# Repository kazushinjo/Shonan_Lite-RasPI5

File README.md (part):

# Shonan for RasPI5

Raspberry Pi 5 + ADALM-PlutoによるDVB-S2 DATV送受信タッチGUIシステム。
本体は`pi5/`配下(Python/PyQt5、eglfs直描画)。

A touch-screen GUI system for DVB-S2 DATV transmission and reception using a Raspberry Pi 5 and an ADALM-Pluto.
The application lives under `pi5/` (Python/PyQt5, rendered directly via eglfs).

> 本READMEは日本語と英語を併記しています。各節で日本語の後に英語が続きます。
> This README is written in both Japanese and English. In each section, the Japanese text is followed by the English text.

> [!IMPORTANT]
> **Plutoのユーザー名(`root`)・パスワード(`analog`)はデフォルト値のまま変更しないでください。**
> 本アプリとLangstone V3は、SSHでPlutoにログインしてリブートしています(アプリ起動時・アプリ再起動・
> 機器試験・Langstone終了時)。変更するとPlutoをリブートできなくなります。
>
> **Keep the Pluto's username (`root`) and password (`analog`) at their default values.**
> This app and Langstone V3 log in to the Pluto via SSH to reboot it (at app start, app restart,
> equipment test and Langstone exit). If they are changed, the Pluto cannot be rebooted.

## 主な機能 / Features

- **送信**: 周波数・シンボルレート(333〜2000 kS/s)・FEC・変調方式(QPSK/8PSK)・TX出力を画面で設定し、
  Pluto内蔵の`pluto_dvb`でDVB-S2送信する。FECは変調方式ごとに実際に動作する組み合わせだけを選べる
  (QPSK: 1/2・3/5・8/9、8PSK: 3/5・8/9)。送信映像はフルHD(1920x1080)固定。
- **映像ソース**: USBカメラ・画像ファイル(静止画を反復送信)・テストパターンから選ぶ。カメラ選択時は
  「撮影」ボタンで静止画(JPG、`~/Pictures/Shonan_Lite/`)を撮り、そのまま送信画像に使える。
  コールサイン・備考を文字サイズ・文字色を選んで映像へ焼き込める(日時も表示)。
- **受信**: GNU Radio(gr-dvbs2rx)によるPi 5上での復調。LOCK状態・ビットレート・パケット数/エラー数を表示。
- **RSSI測定**: 周波数を掃引して受信レベルをグラフ表示する。オンデバイス復調OFF(通常運用)では
  相手局の電波を測り、ON(テスト用)では自局もテストパターンで自動送信して自分の信号を測る。
- **プリセット**: 現在の設定を5件まで登録・呼び出し(プリセット1は未登録の間RFループバック試験用)。
- **10GHz受信(LNB)**: Home画面の衛星をタップすると、Langstone V3を10236.5 MHz表示・
  Pluto受信486.5 MHz(LNB局部発振9750 MHz)の受信専用バンドで開く(下記参照)。
  Shonan_Lite(DATV)でも、周波数画面で「10GHz帯」を押すとLNBを使用するか確認し、使用する場合は
  表示周波数10.2365 GHz・Pluto受信486.5 MHzで受信する(受信専用、送信不可。「いいえ」なら従来どおり10180 MHz)。
- **その他**: Pluto URIの自動検出、日本語/英語表示、日本語オンスクリーンキーボード、アプリ内Help、
  機器試験、起動時のアプリ選択(Shonan_Lite / Langstone V3)。

<!-- English -->

- **Transmit**: Set the frequency, symbol rate (333–2000 kS/s), FEC, modulation (QPSK/8PSK) and TX power on screen,
  and transmit DVB-S2 with `pluto_dvb` running inside the Pluto. Only FEC rates that actually work with each
  modulation can be selected (QPSK: 1/2, 3/5, 8/9; 8PSK: 3/5, 8/9). The transmitted video is fixed at Full HD (1920x1080).
- **Video source**: Choose from a USB camera, an image file (a still image transmitted repeatedly) or a test pattern.
  With the camera selected, the "Capture" button takes a still image (JPG, `~/Pictures/Shonan_Lite/`) that can be
  used directly as the transmit image. A callsign and a note can be burned into the video with a selectable
  text size and color (the date and time are shown as well).
- **Receive**: Demodulation on the Pi 5 with GNU Radio (gr-dvbs2rx). Shows LOCK status, bit rate and packet/error counts.
- **RSSI measurement**: Sweeps the frequency and graphs the received level. With on-device demodulation OFF
  (normal operation) it measures the other station's signal; with it ON (for testing) the station also transmits
  a test pattern automatically and measures its own signal.
- **Presets**: Save and recall up to 5 sets of settings (preset 1 is used for the RF loopback test while it is empty).
- **10 GHz reception (LNB)**: Tapping the satellite on the Home screen opens Langstone V3 on a receive-only band
  showing 10236.5 MHz, with the Pluto receiving at 486.5 MHz (LNB local oscillator 9750 MHz). See below.
  In Shonan_Lite (DATV) as well, pressing "10GHz Band" on the Frequency screen asks whether to use an LNB;
  if so, it receives with the displayed frequency 10.2365 GHz and the Pluto receiving at 486.5 MHz
  (receive only, no transmit; "No" keeps 10180 MHz as before).
- **Other**: Automatic Pluto URI detection, Japanese/English display, Japanese on-screen keyboard, in-app Help,
  equipment test, and application selection at boot (Shonan_Lite / Langstone V3).

## スクリーンショット / Screenshots

実機(7インチLCD、800x480)の画面。映像はすべてテストパターンで撮影している。

Screens from the actual device (7-inch LCD, 800x480). All video was captured using the test pattern.

| Home画面 / Home | 送信画面 / TX | 受信画面 / RX | RSSI測定 / RSSI |
| --- | --- | --- | --- |
|  |  |  |  |

| 映像ソース / Video source | 変調方式 / Modulation | 出力設定 / Stream output | プリセット / Presets |
| --- | --- | --- | --- |
|  |  |  |  |

各画面の操作方法は、アプリ内の「ヘルプ」または操作説明書
[`pi5/docs/shonan_pi5_operation_manual.docx`](pi5/docs/shonan_pi5_operation_manual.docx)を参照。

For how to operate each screen, see the in-app "Help" or the operation manual
[`pi5/docs/shonan_pi5_operation_manual.docx`](pi5/docs/shonan_pi5_operation_manual.docx) (in Japanese).

## インストール / Installation

### 事前に準備するもの / What you need

- Raspberry Pi 5本体
- microSDカードまたはNVMe SSD(Pi5の起動ストレージ)
- 書き込み用PC(Windows/Mac/Linuxいずれか)とmicroSDカードリーダー等
- ADALM-Pluto(DATVファームウェア導入済み)がPi5とEthernet同一ネットワークに
  接続されていること(★`install.sh`実行時点では未接続でもよい。あくまで
  ソフトウェア導入のみで、実運用時に必要)
- 送信映像用USBカメラ・オーディオ機器(任意、無くてもテストパターン映像で
  動作確認できる)

<!-- English -->

- A Raspberry Pi 5
- A microSD card or NVMe SSD (the Pi 5 boot storage)
- A PC for writing the image (Windows, Mac or Linux) and a microSD card reader, etc.
- An ADALM-Pluto (with DATV firmware installed) connected to the same Ethernet network as the Pi 5
  (★It does not need to be connected when running `install.sh`; that only installs software.
  It is required for actual operation.)
- A USB camera and audio devices for the transmitted video (optional; without them you can still
  check operation with the test pattern)

### 0. Raspberry Pi OSのインストール / Installing Raspberry Pi OS

Pi5本体に、あらかじめRaspberry Pi OSをインストールしておく。

1. PCで[Raspberry Pi Imager](https://www.raspberrypi.com/software/)を起動する。
2. 「デバイスを選択」で **Raspberry Pi 5** を選ぶ。
3. 「OSを選択」で **Raspberry Pi OS (64-bit)** を選ぶ
   (★32bit版は不可。下記「実行条件」参照)。
4. 「ストレージを選択」で書き込み先のmicroSD/NVMeを選ぶ。
5. 歯車アイコン(詳細設定)で、ホスト名・ユーザー名/パスワード・Wi-Fi・SSH有効化を
   事前設定しておくと、初回起動後すぐSSH接続できる。
6. 「書き込む」を実行し、完了後microSD/NVMeをPi5に取り付けて起動する。
7. PCから`ssh <ユーザー名>@<ホスト名>.local`で接続できることを確認する。

Install Raspberry Pi OS on the Pi 5 beforehand.

1. Launch [Raspberry Pi Imager](https://www.raspberrypi.com/software/) on your PC.
2. Under "Choose Device", select **Raspberry Pi 5**.
3. Under "Choose OS", select **Raspberry Pi OS (64-bit)**
   (★The 32-bit version is not supported. See "Requirements" below).
4. Under "Choose Storage", select the target microSD/NVMe.
5. If you preset the hostname, username/password, Wi-Fi and SSH in the gear icon (advanced options),
   you can connect via SSH right after the first boot.
6. Click "Write". When done, attach the microSD/NVMe to the Pi 5 and boot it.
7. Confirm that you can connect from your PC with `ssh <username>@<hostname>.local`.

### 0.5 Plutoのネットワーク設定(USB_ETHERNET) / Pluto network settings (USB_ETHERNET)

ADALM-Pluto(DATVファームウェア導入済み)をPi5と同じEthernetネットワークに
接続するには、あらかじめPluto側のUSB_ETHERNETインターフェースに固定IPを
設定しておく。

1. PlutoをPCとUSBケーブルで接続する(USB Mass Storageとして認識される)。
2. Plutoのドライブ直下にある`config.txt`をテキストエディタで開く。
3. `[USB_ETHERNET]`セクションの`ipaddr_eth`と`netmask_eth`を、Pi5と同じ
   サブネット内の値に設定する(例、Pi5が`192.168.0.80/24`の場合)。
4. `config.txt`を保存し、PlutoのドライブをPCから安全に取り出す(eject)。
   Plutoが自動的に再起動し、新しいIPアドレスで起動する。
5. Pi5の設定画面「送信先 (Pluto Tx)」に、ここで設定した`ipaddr_eth`の値
   (下記例では`192.168.0.51`)を入力する。

To connect the ADALM-Pluto (with DATV firmware) to the same Ethernet network as the Pi 5,
assign a static IP to the Pluto's USB_ETHERNET interface beforehand.

1. Connect the Pluto to your PC with a USB cable (it appears as a USB Mass Storage device).
2. Open `config.txt` in the root of the Pluto drive with a text editor.
3. Set `ipaddr_eth` and `netmask_eth` in the `[USB_ETHERNET]` section to values in the same subnet
   as the Pi 5 (example below for a Pi 5 at `192.168.0.80/24`).
4. Save `config.txt` and safely eject the Pluto drive from the PC.
   The Pluto reboots automatically and comes up with the new IP address.
5. Enter the `ipaddr_eth` value set here (`192.168.0.51` in the example below) into
   "Destination (Pluto Tx)" on the Pi 5 settings screen.

```ini
[USB_ETHERNET]
ipaddr_eth = 192.168.0.51
netmask_eth = 255.255.255.0
```

★Plutoのユーザー名(`root`)とパスワード(`analog`)は変更しないこと(理由は冒頭の「IMPORTANT」を参照)。

★Do not change the Pluto's username (`root`) and password (`analog`) (see "IMPORTANT" at the top for why).

★USB直結時のUSB CDCネットワーク(`[NETWORK]`セクション、既定`192.168.2.1`)
とは別の設定である。`[USB_ETHERNET]`は、Pluto(Pluto+)のUSB OTGポートに
挿したUSB-Ethernetアダプタに割り当てるIPアドレスで、これによりPlutoが
Pi5と同じLAN(Ethernet)上のノードとして直接通信できるようになる。
設定ファイルの詳細は
[ADI公式Wiki](https://wiki.analog.com/university/tools/pluto/users/customizing)
を参照。

★This is separate from the USB CDC network used for a direct USB connection (the `[NETWORK]` section,
default `192.168.2.1`). `[USB_ETHERNET]` is the IP address assigned to a USB-Ethernet adapter plugged
into the Pluto (Pluto+) USB OTG port, which lets the Pluto communicate directly as a node on the same
LAN (Ethernet) as the Pi 5. For details of the configuration file, see the
[official ADI Wiki](https://wiki.analog.com/university/tools/pluto/users/customizing).

### 1. install.shの実行 / Running install.sh

本リポジトリはpublicのため、HTTPS clone(`install.sh`既定)でそのまま取得できる。
まずPi5へSSHでログインする(`<...>`の部分はご自身の環境の値に置き換える):

This repository is public, so it can be fetched as-is with an HTTPS clone (the `install.sh` default).
First log in to the Pi 5 via SSH (replace the `<...>` parts with values for your environment):

```sh
ssh <Pi5のユーザー名 / Pi 5 username>@<Pi5のIPアドレスまたはホスト名 / Pi 5 IP address or hostname>
# 例 / Example: ssh pi@192.168.0.80
```

ログイン後、Pi5上で:

After logging in, on the Pi 5:

```sh
# gitが未導入の場合は先に用意する(初回のみ)
# Install git first if it is not installed yet (first time only)
sudo apt-get update && sudo apt-get install -y git

git clone https://github.com/kazushinjo/Shonan_Lite-RasPI5.git
cd Shonan_Lite-RasPI5
./pi5/scripts/install.sh
```

`install.sh`自身も0/9でgit未導入の場合は自動導入する。以降のアップデート時も
このコマンドを再実行するだけでよい(`REPO_BRANCH`環境変数で取得するブランチを
指定できる。既定は`main`)。

`install.sh` itself also installs git automatically at step 0/9 if it is missing. For later updates,
simply re-run this command (the branch to fetch can be specified with the `REPO_BRANCH` environment
variable; the default is `main`).

★自分のフォークやプライベートなミラーからSSH経由で取得したい場合は、
`REPO_URL=git@github.com:<user>/<repo>.git ./pi5/scripts/install_ssh.sh`を使う
(SSH鍵が未登録ならその場で生成し、GitHubへの登録案内を表示して終了する)。

★To fetch from your own fork or a private mirror over SSH, use
`REPO_URL=git@github.com:<user>/<repo>.git ./pi5/scripts/install_ssh.sh`
(if no SSH key is registered, it generates one on the spot, shows instructions for registering it
with GitHub, and exits).

Pi5がGitHubへ到達できない環境(オフライン現場等)では、scp/USB等で転送済みの
ローカルクローンから展開する`install_local.sh`を使う(GitHubへのアクセスは
一切発生しない)。ソース取得部分がgit clone/pullではなくrsyncでのローカル
コピーに変わる以外は`install.sh`と同じ:

Where the Pi 5 cannot reach GitHub (e.g. offline sites), use `install_local.sh`, which installs from
a local clone already transferred via scp/USB etc. (no access to GitHub occurs at all). It is the same
as `install.sh` except that the source is obtained by a local rsync copy instead of git clone/pull:

```sh
./pi5/scripts/install_local.sh
```

さらに、PC側(Windows Git Bash/Mac/Linux)にあらかじめ作っておいたローカル
クローンから、Pi5への転送とインストールを1コマンドで行う`deploy_to_pi5.sh`
もある。PC側でこのリポジトリをclone済みの状態で:

There is also `deploy_to_pi5.sh`, which transfers and installs to the Pi 5 in a single command from a
local clone prepared on your PC (Windows Git Bash/Mac/Linux). With this repository cloned on the PC:

```sh
./pi5/scripts/deploy_to_pi5.sh
# Pi5のIPアドレス/ホスト名: 192.168.1.50   ← 入力 / enter
# Pi5のユーザー名 [pi]:                    ← 入力(空Enterでpi) / enter (empty Enter = pi)
```

を実行すると、Pi5のIPアドレス・ユーザー名の入力だけで、
1. ローカルクローンの中身(`.git`除く)をtar+ssh経由でPi5の`~/shonan-pi5-src`へ転送
2. Pi5上で`install_local.sh`を実行

まで自動で進む。追加ツール(sshpass/rsync)は使わず標準のssh/scp/tarのみで
動くため、Pi5への接続が発生する上記1・2のタイミングでそれぞれ標準のsshパス
ワードプロンプトが表示され、都度パスワードの入力が必要(合計2回。ビルドが
長時間に及ぶ場合、`sudo`のキャッシュが切れて追加でパスワードを求められる
こともある)。都度の入力自体を無くしたい場合はPi5にSSH公開鍵を登録し、
パスワード認証を使わない構成にする。

Just by entering the Pi 5 IP address and username, it automatically:
1. Transfers the contents of the local clone (excluding `.git`) to `~/shonan-pi5-src` on the Pi 5 via tar+ssh
2. Runs `install_local.sh` on the Pi 5

It uses only standard ssh/scp/tar with no extra tools (sshpass/rsync), so the standard ssh password
prompt appears at each of steps 1 and 2 above, where a connection to the Pi 5 is made, and you need
to enter the password each time (twice in total; if the build takes a long time, the `sudo` cache may
expire and ask for the password again). To avoid entering it every time, register an SSH public key
on the Pi 5 and do not use password authentication.

`SHONAN_INSTALL_DIR`・`SKIP_JA_KEYBOARD`・`SKIP_GNURADIO_BUILD`・
`SKIP_LANGSTONE_BUILD`をPC側で環境変数指定すると、Pi5側の`install_local.sh`
実行にもそのまま反映される:

Environment variables `SHONAN_INSTALL_DIR`, `SKIP_JA_KEYBOARD`, `SKIP_GNURADIO_BUILD` and
`SKIP_LANGSTONE_BUILD` set on the PC side are passed through to `install_local.sh` on the Pi 5:

```sh
SKIP_JA_KEYBOARD=1 SKIP_GNURADIO_BUILD=1 ./pi5/scripts/deploy_to_pi5.sh
```

日本語入力ビルド・受信(RX)用GNU Radio/gr-dvbs2rxビルド・Langstone V3ビルドは
それぞれ省略して時間短縮できる(省略した機能は使えなくなる):

The Japanese input build, the GNU Radio/gr-dvbs2rx build for reception (RX) and the Langstone V3
build can each be skipped to save time (skipped features will not be available):

```sh
SKIP_JA_KEYBOARD=1 SKIP_GNURADIO_BUILD=1 SKIP_LANGSTONE_BUILD=1 ./pi5/scripts/install.sh
```

環境変数で挙動を変更できる。

The behavior can be changed with environment variables.

| 変数 / Variable | 既定値 / Default | 効果 / Effect |
| --- | --- | --- |
| `SHONAN_INSTALL_DIR` | `$HOME/shonan-pi5` | リポジトリのclone/pull(またはコピー)先ディレクトリ<br>Directory the repository is cloned/pulled (or copied) into |
| `LOCAL_SOURCE_DIR` | (未設定 / unset) | 設定時、ソース取得をGitHubのclone/pullではなく指定ディレクトリからのrsyncコピーに切り替える(`install_local.sh`が自動設定)<br>When set, obtains the source by rsync copy from the given directory instead of clone/pull from GitHub (set automatically by `install_local.sh`) |
| `QTVK_BUILD_DIR` | `/tmp/qtvirtualkeyboard-src` | Qt Virtual Keyboardのビルド作業ディレクトリ<br>Build working directory for Qt Virtual Keyboard |
| `GR_DVBS2RX_BUILD_DIR` | `$HOME/gr-dvbs2rx` | gr-dvbs2rxのビルド作業ディレクトリ<br>Build working directory for gr-dvbs2rx |
| `SKIP_JA_KEYBOARD` | `0` | `1`で日本語入力ビルド(3/9)を省略<br>`1` skips the Japanese input build (3/9) |
| `SKIP_GNURADIO_BUILD` | `0` | `1`で受信(RX)用GNU Radio/gr-dvbs2rxビルド(4/9)を省略(受信機能は動作しなくなる)<br>`1` skips the GNU Radio/gr-dvbs2rx build for reception (4/9) (reception will not work) |
| `SKIP_LANGSTONE_BUILD` | `0` | `1`でLangstone V3のビルド(5/9)を省略<br>`1` skips the Langstone V3 build (5/9) |

`install.sh`は以下の9ステップを順に実行する(`set -euo pipefail`のため、
いずれかが失敗した時点で即座に停止する)。

`install.sh` runs the following 9 steps in order (because of `set -euo pipefail`, it stops
immediately as soon as any step fails).

| ステップ / Step | 内容 / Description |
| --- | --- |
| 0/9 | 前提条件の確認(git/SSH鍵の有無を確認し、無ければ案内して終了)<br>Check prerequisites (checks for git/SSH key; if missing, shows guidance and exits) |
| 1/9 | ソース取得(`git clone`または`git pull`)<br>Fetch the source (`git clone` or `git pull`) |
| 2/9 | 実行時依存パッケージのインストール(apt)<br>Install runtime dependency packages (apt) |
| 3/9 | 日本語入力(OpenWnn)対応版Qt Virtual Keyboardのビルド(既定で実施、実測10〜20分程度)<br>Build Qt Virtual Keyboard with Japanese input (OpenWnn) support (done by default, about 10–20 minutes measured) |
| 4/9 | 受信(RX)用GNU Radio + gr-dvbs2rxの導入<br>Install GNU Radio + gr-dvbs2rx for reception (RX) |
| 5/9 | Langstone V3(SDRトランシーバー)のビルド<br>Build Langstone V3 (SDR transceiver) |
| 6/9 | 起動時コンソール表示の抑制<br>Suppress the console display at boot |
| 7/9 | reboot/shutdown/起動アプリ切替のパスワード無し実行を許可(sudoers.d)<br>Allow reboot/shutdown/boot-app switching without a password (sudoers.d) |
| 8/9 | 電源電圧警告(稲妻アイコン)表示の抑制(`/boot/firmware/config.txt`)<br>Suppress the under-voltage warning (lightning icon) (`/boot/firmware/config.txt`) |
| 9/9 | systemdサービス登録(`shonan-gui.service`/`langstone.service`/`shonan-boot-menu.service`)<br>Register systemd services (`shonan-gui.service`/`langstone.service`/`shonan-boot-menu.service`) |

途中で通信・電源が切れない環境で実行すること。完了後、起動のたびに
「Shonan_Lite / Langstone V3」を選ぶ全画面メニュー
(`shonan-boot-menu.service`)が自動起動する。選んだ側の`shonan-gui.service`/
`langstone.service`をsystemdに登録・起動する。あわせて
`/boot/firmware/config.txt`へ`avoid_warnings=1`(電源電圧警告アイコンの表示抑制)
を未設定なら自動で追記する(反映には再起動が必要)。

Run it in an environment where the network and power will not be interrupted. After completion,
a full-screen menu for choosing "Shonan_Lite / Langstone V3" (`shonan-boot-menu.service`) starts
automatically at every boot, and the selected `shonan-gui.service`/`langstone.service` is registered
with systemd and started. It also appends `avoid_warnings=1` (suppresses the under-voltage warning
icon) to `/boot/firmware/config.txt` if not already set (a reboot is required for it to take effect).

### インストール後の確認 / After installation

インストールが終わったら、まず実機のホーム画面から「ヘルプ」を開いて
使い方を確認する。画面構成、送受信の基本操作、設定項目、トラブルシュー
ティング等の各章が実機の現在の仕様に合わせてまとまっている。

After installation, first open "Help" from the Home screen on the device and review how to use it.
Chapters on the screen layout, basic TX/RX operation, settings, troubleshooting and more are kept up
to date with the current behavior of the device.

## 実機LCDの画面キャプチャー / Capturing the device LCD screen

### アプリ内蔵のスクリーンショット機能(推奨) / Built-in screenshot function (recommended)

Shonan_Lite(GUI)は起動中、Unixドメインソケット`/tmp/shonan-pi5-gui.sock`でコマンドを受け付ける。
`screenshot`を送ると、表示中の画面を`/tmp/shonan_lcd_actual.png`に保存する(GUIは止まらない)。
`navigate:<画面名>`で任意の画面へ移動できる(画面名: `home` `tx` `rx` `frequency` `rssi`
`symbolrate` `fec` `modulation` `videosource` `streamoutput` `rxgain` `txpower` `manual`
`settings` `testequipment` `presets`)。
`volume:<増減>`(例: `volume:+2`)は、ロータリーエンコーダを回したときと同じ音量変更を行う(音量ポップアップの確認用)。

While running, Shonan_Lite (GUI) accepts commands on the Unix domain socket `/tmp/shonan-pi5-gui.sock`.
Sending `screenshot` saves the current screen to `/tmp/shonan_lcd_actual.png` (the GUI does not stop).
`navigate:<screen>` moves to any screen (screens: `home` `tx` `rx` `frequency` `rssi`
`symbolrate` `fec` `modulation` `videosource` `streamoutput` `rxgain` `txpower` `manual`
`settings` `testequipment` `presets`).
`volume:<delta>` (e.g. `volume:+2`) changes the volume the same way as turning the rotary encoder (for checking the volume popup).

```bash
python3 -c "import socket,sys; s=socket.socket(socket.AF_UNIX); s.connect('/tmp/shonan-pi5-gui.sock'); s.sendall(sys.argv[1].encode()); s.close()" navigate:rssi
python3 -c "import socket,sys; s=socket.socket(socket.AF_UNIX); s.connect('/tmp/shonan-pi5-gui.sock'); s.sendall(sys.argv[1].encode()); s.close()" screenshot
```

起動直後は「アプリ起動時にPlutoも再起動しています…」の表示(最大25秒)が写ることがあるので、
起動から30秒ほど待ってから撮る。

Right after startup, the message "Rebooting the Pluto as the app starts…" (up to 25 seconds) may be
captured, so wait about 30 seconds after startup before taking a screenshot.

### kmsgrabによる取得 / Capturing with kmsgrab

Shonan_LiteはLCDへQt/DRMで直接描画しているため、`/dev/fb0`を読み出す方法では
起動コンソールなど、最終合成前の内容になることがある(素の色1色などになる)。
実際にLCDへ表示されている画面を取得する場合は、KMSのCRTC/Planeを指定して
`ffmpeg`の`kmsgrab`を使う。

Because Shonan_Lite draws directly to the LCD via Qt/DRM, reading `/dev/fb0` may give content from
before final composition, such as the boot console (e.g. a single plain color). To capture what is
actually displayed on the LCD, use `ffmpeg`'s `kmsgrab` specifying the KMS CRTC/Plane.

★`/dev/dri/card0`はモードセッティング非対応のスタブデバイスで、これを指定すると
`kmsgrab`が`Failed to set universal planes capability`/`Operation not supported`
で失敗する(実機で確認)。DSIパネルを実際に駆動しているのは**`/dev/dri/card1`**
なので、必ずこちらを指定する。

★`/dev/dri/card0` is a stub device without mode-setting support; specifying it makes `kmsgrab` fail
with `Failed to set universal planes capability`/`Operation not supported` (confirmed on the device).
The DSI panel is actually driven by **`/dev/dri/card1`**, so always specify that one.

まず実機で現在のCRTC/Plane IDを確認する(再起動などでIDが変わる場合がある):

First check the current CRTC/Plane IDs on the device (the IDs may change after a reboot, etc.):

```bash
kmsprint
```

現在の実機ではCRTC IDが`36`、Plane IDが`34`なので、以下でLCD画面をPNG化できる。
`sudo`のパスワード入力が必要になる。

On the current device the CRTC ID is `36` and the Plane ID is `34`, so the following saves the LCD
screen as a PNG. You will need to enter the `sudo` password.

```bash
sudo ffmpeg -y -hide_banner \
  -f kmsgrab -device /dev/dri/card1 \
  -crtc_id 36 -plane_id 34 -framerate 1 -i - \
  -vf hwdownload,format=bgr0 -frames:v 1 -update 1 /tmp/shonan_lcd_actual.png
```

MacなどのPCへコピーする:

Copy it to a PC such as a Mac:

```bash
scp pi@<Pi5のIPアドレス / Pi 5 IP address>:/tmp/shonan_lcd_actual.png \
  ~/Desktop/shonan_lcd_actual.png
```

`/dev/fb0`の直接取得は、LCDの最終表示を取得できない場合があるため、実機LCDの
スクリーンショットには使用しない。

Reading `/dev/fb0` directly may not capture the final LCD image, so do not use it for screenshots
of the device LCD.

### 実行条件 / Requirements

一般ユーザーが実行して`install.sh`が正常完了するには、以下が必要。

- **Raspberry Pi OS 64bit(aarch64)であること**(32bit版不可)
- **`git`が事前にインストール済み**であること
- **GitHub/apt配布ミラーへのインターネット到達性**
- **sudoが使える対話的な実行**(パスワード入力に応答できるtty)
- **`patch`コマンドが使えること**

詳細な各手順の解説・トラブルシュートは
[`pi5/docs/install_script_guide.md`](pi5/docs/install_script_guide.md)
(DOCX版: `pi5/docs/install_script_guide.docx`)を参照。

For `install.sh` to complete successfully when run by a regular user, the following are required:

- **Raspberry Pi OS 64-bit (aarch64)** (the 32-bit version is not supported)
- **`git` installed beforehand**
- **Internet access to GitHub and the apt mirrors**
- **Interactive execution with sudo available** (a tty that can answer password prompts)
- **The `patch` command available**

For a detailed explanation of each step and troubleshooting, see
[`pi5/docs/install_script_guide.md`](pi5/docs/install_script_guide.md)
(DOCX version: `pi5/docs/install_script_guide.docx`, in Japanese).

## Langstone V3(SDRトランシーバー)への切替 / Switching to Langstone V3 (SDR transceiver)

Pi5起動後にまず表示される「起動するアプリを選択してください」メニュー
(`shonan-boot-menu.service`)、またはShonan_Lite Home画面の「Langstone V3」
ボタンから、[g4eml/Langstone-V3](https://github.com/g4eml/Langstone-V3)
(VHF/UHF/マイクロ波帯SDRトランシーバー、ADALM-Pluto対応)へ切り替えられる。
Langstone V3はQt eglfsとは別に`/dev/fb0`を直接描画する独立アプリのため、
DATV送受信アプリとは同時起動できないが、**`shonan-gui.service`/
`langstone.service`/`shonan-boot-menu.service`がsystemdの`Conflicts=`で
互いに排他制御されているため、Pi5自体のrebootは不要**で
`systemctl start`だけで即座に切り替わる(以前はPi5ごとrebootしていたが、
`shonan-boot-menu.service`導入により不要になった)。

- Shonan_Lite Home画面の「Langstone V3」ボタン → Langstone V3が起動
  (現在稼働中のShonan_Liteプロセスはsystemdが自動停止)
- Langstone V3の設定メニュー内「BACK TO SHONAN_LITE」ボタン →
  Shonan_Lite Home画面に戻る

From the "Select the app to start" menu shown first after the Pi 5 boots (`shonan-boot-menu.service`),
or from the "Langstone V3" button on the Shonan_Lite Home screen, you can switch to
[g4eml/Langstone-V3](https://github.com/g4eml/Langstone-V3) (a VHF/UHF/microwave SDR transceiver
supporting the ADALM-Pluto). Langstone V3 is a standalone app that draws directly to `/dev/fb0`,
separately from Qt eglfs, so it cannot run at the same time as the DATV app. However,
**`shonan-gui.service`/`langstone.service`/`shonan-boot-menu.service` are mutually exclusive via
systemd `Conflicts=`, so no reboot of the Pi 5 is needed**; a `systemctl start` switches immediately
(previously the whole Pi 5 was rebooted, but this became unnecessary with `shonan-boot-menu.service`).

- "Langstone V3" button on the Shonan_Lite Home screen → Langstone V3 starts
  (systemd automatically stops the running Shonan_Lite process)
- "BACK TO SHONAN_LITE" button in the Langstone V3 settings menu →
  returns to the Shonan_Lite Home screen

切替時にPluto(とPA_Power/PTTコントローラの12V電源)は**再起動しない**
(以前は切替のたびにPlutoを再起動しており、数十秒かかっていた)。実機試験で、
DATV→Langstone→DATVとPlutoを再起動せずに切り替えても、Langstoneの送受信と
DATVの送受信(オンデバイス復調による自局信号のロック)が正常に動くことを確認した。
ただしLangstoneは受信中にPlutoの送信LO(`altvoltage1`)をpowerdownしたまま終了し、
そのままではDATV送信の電波が出ないため、「GOTO SHONAN_LITE」で戻るときは
Langstone側とShonan_Lite側の両方で送信LOを元に戻す。
Langstoneからの切替であることは`/tmp/shonan_switch_from_langstone`で伝え、
Shonan_Liteはこれがあるときだけ起動時のPluto再起動を省く(使ったら消すので、
その後のアプリ再起動やPi5の電源投入時は従来どおり再起動する)。Langstone側の
`run_pluto`は`/tmp/langstone_goto_shonan`があるとき、終了後のPluto再起動を省く。Plutoが`fmcomms2_source: Unable to refill buffer`のように
詰まった場合は、Home画面の「アプリ再起動」(Plutoも再起動する)で復旧できる。

The Pluto (and the 12 V supply of the PA_Power/PTT controller) is **not rebooted** when switching
(previously the Pluto was rebooted on every switch, which took tens of seconds). Device testing
confirmed that after switching DATV → Langstone → DATV without rebooting the Pluto, both Langstone
TX/RX and DATV TX/RX (locking onto the station's own signal with on-device demodulation) work
correctly. However, Langstone exits with the Pluto's TX LO (`altvoltage1`) still powered down while
receiving, which would leave DATV transmission with no RF output, so when returning via
"GOTO SHONAN_LITE" both the Langstone side and the Shonan_Lite side restore the TX LO.
A switch from Langstone is signaled by `/tmp/shonan_switch_from_langstone`, and Shonan_Lite skips the
Pluto reboot at startup only when it exists (it is deleted after use, so later app restarts and Pi 5
power-ups reboot the Pluto as before). On the Langstone side, `run_pluto` skips the Pluto reboot after
exiting when `/tmp/langstone_goto_shonan` exists. If the Pluto gets stuck, e.g. with
`fmcomms2_source: Unable to refill buffer`, it can be recovered with "Restart App" on the Home screen
(which also reboots the Pluto).

内部的には`~/.pi5_boot_mode_langstone`マーカーファイルの有無をsystemdの
`ConditionPathExists`で判定し、`shonan-gui.service`/`langstone.service`の
どちらを起動すべきかを決める(ブート時だけでなく、アプリ内からの切替時にも
マーカーを書き換えてから対象サービスを直接startする)。

Internally, systemd's `ConditionPathExists` checks for the `~/.pi5_boot_mode_langstone` marker file
to decide whether `shonan-gui.service` or `langstone.service` should start (not only at boot; when
switching from within an app, the marker is rewritten and the target service is started directly).

ウォーターフォール/スペクトラム表示は幅約512px→約790pxへ拡張済み
(FFT点数自体はGNU Radio側のfft_size=512のまま、SCALEPX()マクロで描画のみ
引き伸ばしている。帯域インジケータ・目盛り・タッチ判定も含め一貫して変換)。
横方向にはSQLボタン(x=30〜130)/Volボタン(x=660〜)と同じY帯で重なり広げる
余地が無かったため、スペクトラム欄の高さ(80→55px)とウォーターフォールの
表示履歴行数(130→90行)を縮めて表示位置を上に詰め、SQL/Vol/RITいずれとも
Y方向に重ならない帯(Y=130〜295)に収めることで横方向をほぼ画面全幅まで
広げた(実機で確認、詳細は下記パッチ参照)。
詳細は
[`pi5/docs/patches/langstone_v3_shonan_lite.patch`](pi5/docs/patches/langstone_v3_shonan_lite.patch)
(upstream差分)を参照。

The waterfall/spectrum display has been widened from about 512 px to about 790 px
(the number of FFT points stays at fft_size=512 on the GNU Radio side; only the drawing is stretched
by the SCALEPX() macro, applied consistently to the bandwidth indicator, scale and touch detection).
Since there was no room to widen it horizontally in the same Y band as the SQL button (x=30–130) and
Vol button (x=660–), the spectrum area height (80 → 55 px) and the number of waterfall history rows
(130 → 90) were reduced and the display moved up, fitting it into a band (Y=130–295) that does not
overlap SQL/Vol/RIT vertically, which allows it to extend to nearly the full screen width (confirmed
on the device). For details, see
[`pi5/docs/patches/langstone_v3_shonan_lite.patch`](pi5/docs/patches/langstone_v3_shonan_lite.patch)
(diff against upstream).

起動直後の受信設定の取りこぼしも修正済み。本家のGUIは、GNU Radioフローグラフが
受信設定用のFIFO(`/tmp/langstoneTRx`)を開く前にモード・フィルタ・オフセット等を送り、
届かなかった分を捨てていた。そのためフローグラフが初期値(USB・オフセット0等)のまま動き、
Sメーター・ノイズレベルが本来より高く出ることがあった(Shonan_Liteから切り替えた直後に
S2前後、MODEやBANDを操作し直すとS0になる、を実機で確認)。オフセット0ではLO直上に出る
PlutoのDC成分(DCのこぶ)を受信帯域内で拾うためで、正しい値はS0の方
(本来はLOを+50 kHzずらしてDC成分を避ける。TX→40 dBアッテネータ→RXの無信号状態でS0)。
起動時にフローグラフがFIFOを開くまで(最大20秒)待ってから設定を送るようにした
(`waitForFlowgraph()`)。なおSメーターの0点(`S-Meter Zero`)は既定値-80のままで、
絶対レベル(S9=-73 dBm等)としては未校正。

The loss of receive settings right after startup has also been fixed. The upstream GUI sent the mode,
filters, offset, etc. before the GNU Radio flowgraph opened its settings FIFO (`/tmp/langstoneTRx`)
and discarded whatever could not be delivered, so the flowgraph kept running with its defaults
(USB, offset 0, etc.) and the S-meter and noise level could read higher than they should (confirmed
on the device: about S2 right after switching from Shonan_Lite, S0 after pressing MODE or BAND again).
With offset 0 the receiver picks up the Pluto's DC component (the DC hump right at the LO) inside the
passband, so S0 is the correct reading (normally the LO is shifted by +50 kHz to avoid the DC
component; with TX → 40 dB attenuator → RX and no signal it reads S0).
At startup it now waits until the flowgraph opens the FIFO (up to 20 s) before sending the settings
(`waitForFlowgraph()`). Note that the S-meter zero (`S-Meter Zero`) is still at its default of -80,
so it is not calibrated as an absolute level (e.g. S9 = -73 dBm).

`g4eml/Langstone-V3`本家が更新された場合、`pi5/third_party/Langstone-V3/`を
直接上書きすると上記の改造が失われる。
[`pi5/scripts/update_langstone_from_upstream.sh`](pi5/scripts/update_langstone_from_upstream.sh)
を実行すると、本家を読み取り専用でclone → このパッチを適用 →
成功した場合のみ`pi5/third_party/Langstone-V3/`を置き換える(本家への
書き込みは一切行わない)。パッチが当たらない場合は改造箇所と本家の変更が
衝突しているため、エラーで止まり手動マージが必要になる。

When upstream `g4eml/Langstone-V3` is updated, overwriting `pi5/third_party/Langstone-V3/` directly
would lose the modifications above. Running
[`pi5/scripts/update_langstone_from_upstream.sh`](pi5/scripts/update_langstone_from_upstream.sh)
clones upstream read-only → applies this patch → replaces `pi5/third_party/Langstone-V3/` only if
that succeeds (nothing is ever written to upstream). If the patch does not apply, the modifications
conflict with upstream changes; it stops with an error and a manual merge is required.

### 10GHz受信(LNB) — Home画面の衛星をタップ / 10 GHz reception (LNB) — tap the satellite on the Home screen

Home画面の背景右側の衛星をタップすると、Langstone V3を**10GHz受信用のバンド**で
開く(普通の「Langstone」カードと同じく、Plutoは再起動しない)。アンテナ側で
**LNB(局部発振 9750 MHz)**により周波数を下げて受信する前提の設定で、
LangstoneのトランスバーターのオフセットとしてLNBの局部発振周波数を設定している。

Tapping the satellite on the right side of the Home screen background opens Langstone V3 on a
**band for 10 GHz reception** (as with the normal "Langstone" card, the Pluto is not rebooted).
The settings assume the frequency is down-converted at the antenna by an **LNB (local oscillator
9750 MHz)**, and the LNB local oscillator frequency is set as Langstone's transverter offset.

| 項目 / Item | 値 / Value |
| --- | --- |
| 画面の表示周波数<br>Displayed frequency | 10236.500 MHz(10.2365 GHz、画面に「XVTR」と表示)<br>10236.500 MHz (10.2365 GHz, "XVTR" shown on screen) |
| Plutoの受信周波数<br>Pluto receive frequency | 486.5 MHz(= 10236.5 − 9750) |
| 受信オフセット<br>Receive offset | −9750 MHz(LNB 局部発振 9750 MHz)<br>−9750 MHz (LNB local oscillator 9750 MHz) |
| 受信モード<br>Receive mode | 固定しない(Langstoneの「MODE」でUSB/FM/CW等を選べる)<br>Not fixed (USB/FM/CW etc. can be selected with Langstone's "MODE") |
| 送信<br>Transmit | **不可**(受信専用)<br>**Not possible** (receive only) |

- Langstoneの24バンドのうち、通常使われない最後のバンド(番号23、画面上は24番目)を
  このために使う。衛星をタップするたびに、Shonan_Liteが`~/Langstone/Langstone_Pluto.conf`
  のこのバンドを上の値に設定し直してから開く([`pi5/gui/langstone_config.py`](pi5/gui/langstone_config.py))。
- 486.5 MHzはアマチュアバンド外のため、このバンドは**受信専用**
  (設定ファイルの`bandRxOnly23 1`、Langstone側の改造)。画面のPTT・ハードウェアPTT・
  CWキー・ビーコンのいずれでも送信せず、PA_Power/PTTコントローラも送信に切り替えない。
  PTTボタンは灰色の「RX ONLY」表示になり、Plutoの送信LOも停止させる。
- 普通の「Langstone」カードで開いたときは、衛星から開く前に使っていたバンドに戻して開く
  (Langstone上で別のバンドに切り替えていた場合は、そのバンドのまま)。
- LNBへの電源供給(同軸経由のバイアスT、12〜18 V)はShonan_Lite/Langstoneでは扱わない。
  別途用意すること。
- Shonan_Lite(DATV)で10GHzをLNB受信する場合は、衛星ではなく周波数画面の「10GHz帯」を押し、
  「LNBを使用しますか?」で「はい」を選ぶ(表示10.2365 GHz、Pluto受信486.5 MHz、受信専用で送信不可。
  受信画面・RSSI測定もPluto受信周波数で動作する)。他のバンドを選ぶとLNBは解除される。

<!-- English -->

- Of Langstone's 24 bands, the last one, which is not normally used (number 23, the 24th on screen),
  is used for this. Every time the satellite is tapped, Shonan_Lite resets this band in
  `~/Langstone/Langstone_Pluto.conf` to the values above before opening
  ([`pi5/gui/langstone_config.py`](pi5/gui/langstone_config.py)).
- Because 486.5 MHz is outside the amateur bands, this band is **receive only**
  (`bandRxOnly23 1` in the configuration file, a modification on the Langstone side). It does not
  transmit from the on-screen PTT, hardware PTT, CW key or beacon, and does not switch the
  PA_Power/PTT controller to transmit. The PTT button is shown grayed out as "RX ONLY", and the
  Pluto's TX LO is also stopped.
- When opened from the normal "Langstone" card, it returns to the band that was in use before opening
  from the satellite (if you switched to another band in Langstone, it stays on that band).
- Power for the LNB (bias-T over the coax, 12–18 V) is not handled by Shonan_Lite/Langstone.
  Provide it separately.
- To receive 10 GHz via an LNB in Shonan_Lite (DATV), press "10GHz Band" on the Frequency screen
  (not the satellite) and answer "Yes" to "Use an LNB?" (displayed 10.2365 GHz, Pluto RX 486.5 MHz,
  receive only with no transmit; the RX screen and RSSI measurement also use the Pluto RX frequency).
  Selecting another band cancels the LNB.

## オプション: ESP32 W5500(PA_Power/PTTコントローラ) / Option: ESP32 W5500 (PA_Power/PTT controller)

ESP32とW5500(有線LAN)で、PA等の12 V電源とPTTをLAN経由でON/OFFするオプションの制御基板。
使わなくてもShonan_Liteは動作する(PTTだけなら下記のPi 5 GPIO21で切替できる)。
ファームウェアは[`hardware/W5500_PA_PTT_Control/W5500_PA_PTT_Control.ino`](hardware/W5500_PA_PTT_Control/W5500_PA_PTT_Control.ino)、
基板は[`hardware/W5500_PA_PTT_Control/kicad/`](hardware/W5500_PA_PTT_Control/kicad/)(KiCad、Rev.1.0)。

| 基板の3D表示 / 3D view of the board | 基板レイアウト(KiCad) / PCB layout (KiCad) | ケース(OpenSCAD) / Case (OpenSCAD) |
| --- | --- | --- |
|  |  |  |

| 項目<br>Item | 内容<br>Details |
| --- | --- |
| 構成<br>Configuration | Freenove ESP32-WROOM-32E DevKitC(ソケットに差し込み)+W5500 Lite(SPI接続)<br>Freenove ESP32-WROOM-32E DevKitC (plugged into a socket) + W5500 Lite (SPI) |
| 12 V電源<br>12 V power | 2SJ334(Pチャネル MOSFET)のハイサイドスイッチでJ5の12 V出力をON/OFF。放熱器付きで目安は約7 Aまで<br>J5's 12 V output is switched by a 2SJ334 (P-channel MOSFET) high-side switch; with its heatsink, up to about 7 A |
| PTT<br>PTT | 2SC1815で無線機のPTT端子をGNDへ落とす(J6)<br>A 2SC1815 pulls the radio's PTT line to GND (J6) |
| 電源入力<br>Power input | +12 V(13.8 V系)をJ2へ。L7805で5 V(ESP32)、TA48033Sで3.3 V(W5500)を作る<br>+12 V (13.8 V class) to J2; an L7805 makes 5 V (ESP32) and a TA48033S makes 3.3 V (W5500) |
| 表示LED<br>Indicator LEDs | 外付け。J7=12 V出力(赤)、J8=12 V入力(緑)(JST XH)<br>External; J7 = 12 V output (red), J8 = 12 V input (green) (JST XH) |
| ネットワーク<br>Network | 固定IP(初期値`192.168.0.100`)。ブラウザで`http://<IP>/config`を開くとIPや遅延時間を変更できる<br>Static IP (default `192.168.0.100`); open `http://<IP>/config` in a browser to change the IP and delays |
| 基板<br>Board | 72×115 mm、4層(内層はGNDと+12Vのベタ)、部品はすべてスルーホール。JLCPCBの発注データは[`fabrication/jlcpcb/`](hardware/W5500_PA_PTT_Control/fabrication/jlcpcb/)<br>72×115 mm, 4 layers (inner layers are GND and +12 V planes), all through-hole parts. JLCPCB order data is in [`fabrication/jlcpcb/`](hardware/W5500_PA_PTT_Control/fabrication/jlcpcb/) |
| ケース<br>Case | OpenSCAD(LAN_PTT.scad)、内寸80×120×35 mm。前面にRJ45の角穴と+12V入力の丸型コネクタ、背面にUSBの穴と12 V出力・PTTの丸型コネクタ<br>OpenSCAD (LAN_PTT.scad), inside 80×120×35 mm. RJ45 opening and +12 V input circular connector on the front; USB opening and 12 V output/PTT circular connector on the back |

Shonan_Liteでの使い方:

- 設定画面の「PA_Power/PTTコントローラ (ESP32)」で「ESP32 W5500を使用する」をONにし、ESP32のIPアドレスを入力する。
- アプリの起動/終了に連動して12 V電源(Pluto含む)を、送信開始/終了に連動してPTTを自動でON/OFFする。
- ホーム画面の「Pluto電源」カードで、12 V系統を手動で電源サイクル(OFF→3秒待機→ON)できる。

詳しくは[仕様書](hardware/W5500_PA_PTT_Control/docs/W5500_PA_PTT_Control_仕様書.md)と
[接続一覧](hardware/W5500_PA_PTT_Control/docs/MCU1_J1_W5500_接続一覧.md)を参照(どちらも日英併記。Word版・PDF版も同じフォルダにある)。
回路図: [`w5500-esp32.pdf`](hardware/W5500_PA_PTT_Control/kicad/w5500-esp32.pdf)、
実装図: [`w5500-esp32_実装図_部品番号.pdf`](hardware/W5500_PA_PTT_Control/fabrication/assembly/w5500-esp32_実装図_部品番号.pdf)。

> [!NOTE]
> ESP32への書き込みと起動は確認済み。12 V電源・PTTの駆動回路と無線機をつないだ実地試験はまだ行っていない。

<!-- English -->

An optional control board that uses an ESP32 and a W5500 (wired LAN) to switch the 12 V power for the PA etc.
and the PTT ON/OFF over the LAN. Shonan_Lite works without it (PTT alone can be switched with the Pi 5 GPIO21 below).
The firmware is [`hardware/W5500_PA_PTT_Control/W5500_PA_PTT_Control.ino`](hardware/W5500_PA_PTT_Control/W5500_PA_PTT_Control.ino)
and the board is in [`hardware/W5500_PA_PTT_Control/kicad/`](hardware/W5500_PA_PTT_Control/kicad/) (KiCad, Rev.1.0).

How to use it with Shonan_Lite:

- On the Settings screen, turn on "Use ESP32 W5500" under "PA_Power/PTT Controller (ESP32)" and enter the ESP32's IP address.
- The 12 V power (including the Pluto) is switched ON/OFF with app start/exit, and the PTT with TX start/stop.
- The "Pluto Power" card on the Home screen power-cycles the 12 V line manually (OFF → wait 3 s → ON).

For details, see the [specification](hardware/W5500_PA_PTT_Control/docs/W5500_PA_PTT_Control_仕様書.md) and the
[connection list](hardware/W5500_PA_PTT_Control/docs/MCU1_J1_W5500_接続一覧.md) (both in Japanese and English;
Word and PDF versions are in the same folder).
Schematic: [`w5500-esp32.pdf`](hardware/W5500_PA_PTT_Control/kicad/w5500-esp32.pdf);
assembly drawing: [`w5500-esp32_実装図_部品番号.pdf`](hardware/W5500_PA_PTT_Control/fabrication/assembly/w5500-esp32_実装図_部品番号.pdf).

> [!NOTE]
> Flashing and booting the ESP32 have been confirmed. A field test with the 12 V power/PTT drive circuits
> connected to a radio has not been done yet.

## PA/LNAの送受信切替(ESP32 W5500なしでも可) / PA/LNA TX/RX switching (possible without ESP32 W5500)

ESP32 W5500(PA_Power/PTTコントローラ、[`hardware/W5500_PA_PTT_Control`](hardware/W5500_PA_PTT_Control))は
使わなくても、RasPI5からのPTT ON信号でPA・LNAの送受信切替を制御できる。

| 項目<br>Item | 内容<br>Details |
| --- | --- |
| 出力ピン<br>Output pin | Pi 5 GPIO21(40番ピン)、GNDは39番ピン<br>Pi 5 GPIO21 (pin 40), GND on pin 39 |
| 論理<br>Logic | 送信中HIGH(3.3 V)、受信中LOW<br>HIGH (3.3 V) while transmitting, LOW while receiving |
| 対象<br>Applies to | Shonan_Liteの送信・Langstone V3の送信(Langstone標準のTx Output)のどちらも同じピン<br>Both Shonan_Lite TX and Langstone V3 TX (Langstone's standard Tx Output) use the same pin |

- GPIO21は3.3 Vロジックで電流を取れないため、トランジスタやリレードライバ等でバッファしてから
  PA・LNA(同軸リレー等)を駆動すること。
- Shonan_Liteは送信開始時(映像送出の前)にHIGH、送信停止時とアプリ起動時にLOWにする
  ([`pi5/gui/backend.py`](pi5/gui/backend.py)の`_set_pi5_tx_gpio()`)。Langstone V3はHIGHにしてから
  100 ms後に送信を始める。
- ESP32 W5500を併用する場合は、ESP32のPTT出力(J6)も従来どおり同時に切り替わる。
  12 V電源のON/OFFとホーム画面の「Pluto電源」カードはESP32 W5500が必要。

<!-- English -->

The PA and LNA can be switched between TX and RX by the PTT ON signal from the RasPI5, even without the
ESP32 W5500 (PA_Power/PTT controller, [`hardware/W5500_PA_PTT_Control`](hardware/W5500_PA_PTT_Control)).

- GPIO21 is a 3.3 V logic output that cannot supply current. Buffer it with a transistor, relay driver or
  similar before driving the PA and LNA (coax relays, etc.).
- Shonan_Lite sets it HIGH when TX starts (before the video is sent) and LOW when TX stops and at app startup
  (`_set_pi5_tx_gpio()` in [`pi5/gui/backend.py`](pi5/gui/backend.py)). Langstone V3 starts transmitting
  100 ms after setting it HIGH.
- When the ESP32 W5500 is also used, its PTT output (J6) switches at the same time as before.
  Switching the 12 V power ON/OFF and the "Pluto Power" card on the Home screen still require the ESP32 W5500.

## 関連ドキュメント / Related documents

- [`pi5/docs/install_script_guide.md`](pi5/docs/install_script_guide.md) — install.shの詳細ガイド / Detailed guide to install.sh(英語版 / English: [`install_script_guide_en.md`](pi5/docs/install_script_guide_en.md))
- [`pi5/docs/qtvirtualkeyboard_ja_build.md`](pi5/docs/qtvirtualkeyboard_ja_build.md) — 日本語オンスクリーンキーボードのビルド手順・ハマりどころ / Build steps and pitfalls for the Japanese on-screen keyboard
- [`pi5/docs/shonan_pi5_operation_manual.docx`](pi5/docs/shonan_pi5_operation_manual.docx) — 操作説明書(各画面のスクリーンショット付き) / Operation manual (with screenshots of each screen)
- [`pi5/gui/manual_content.py`](pi5/gui/manual_content.py) — アプリ内Helpの内容(章データ)。操作説明書もこれから生成する / Content of the in-app Help (chapter data); the operation manual is also generated from it
- [`pi5/docs/build_operation_manual.py`](pi5/docs/build_operation_manual.py) — 操作説明書(DOCX)の生成スクリプト / Script that generates the operation manual (DOCX)
  (`python pi5/docs/build_operation_manual.py`、python-docxが必要 / requires python-docx)
- [`hardware/W5500_PA_PTT_Control/docs/W5500_PA_PTT_Control_仕様書.md`](hardware/W5500_PA_PTT_Control/docs/W5500_PA_PTT_Control_仕様書.md) — ESP32 W5500(PA_Power/PTTコントローラ)の仕様書 / Specification of the ESP32 W5500 (PA_Power/PTT controller)(日英併記 / Japanese and English)
  - 仕様書・接続一覧のWord版・PDF版は[`hardware/W5500_PA_PTT_Control/docs/tools/build_docs.py`](hardware/W5500_PA_PTT_Control/docs/tools/build_docs.py)でMarkdownから作る(macOSで実行) / The Word and PDF versions of the specification and connection list are generated from Markdown with this script (run on macOS)
- [`hardware/W5500_PA_PTT_Control/docs/MCU1_J1_W5500_接続一覧.md`](hardware/W5500_PA_PTT_Control/docs/MCU1_J1_W5500_接続一覧.md) — ESP32・W5500の接続一覧 / Connection list of the ESP32 and W5500(日英併記 / Japanese and English)
- [`pi5/third_party/rpi-dvbs2-receiver-gui/`](pi5/third_party/rpi-dvbs2-receiver-gui/) — GNU Radio/gr-dvbs2rx受信フローグラフの参考実装(kazushinjo/rpi-dvbs2-receiver-guiより取り込み) / Reference implementation of the GNU Radio/gr-dvbs2rx receive flowgraph (imported from kazushinjo/rpi-dvbs2-receiver-gui)

## 免責事項 / Disclaimer

1. **無保証・自己責任 / No warranty; use at your own risk**  
   本ソフトウェアは現状のまま(AS IS)で提供され、動作、品質、特定の目的への適合性を含め、いかなる保証もありません。本ソフトウェアの使用または使用できないことによって生じた、機器の破損、データの消失、電波障害、その他一切の損害について、開発者は責任を負いません。ご自身の責任においてご利用ください。  
   This software is provided "AS IS" without warranty of any kind, including any warranty of operation, quality or fitness for a particular purpose. The developers accept no liability for any damage arising from the use of, or inability to use, this software, including damage to equipment, loss of data and radio interference. Use it at your own risk.
2. **免許と法令の順守 / Licensing and compliance with the law**  
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
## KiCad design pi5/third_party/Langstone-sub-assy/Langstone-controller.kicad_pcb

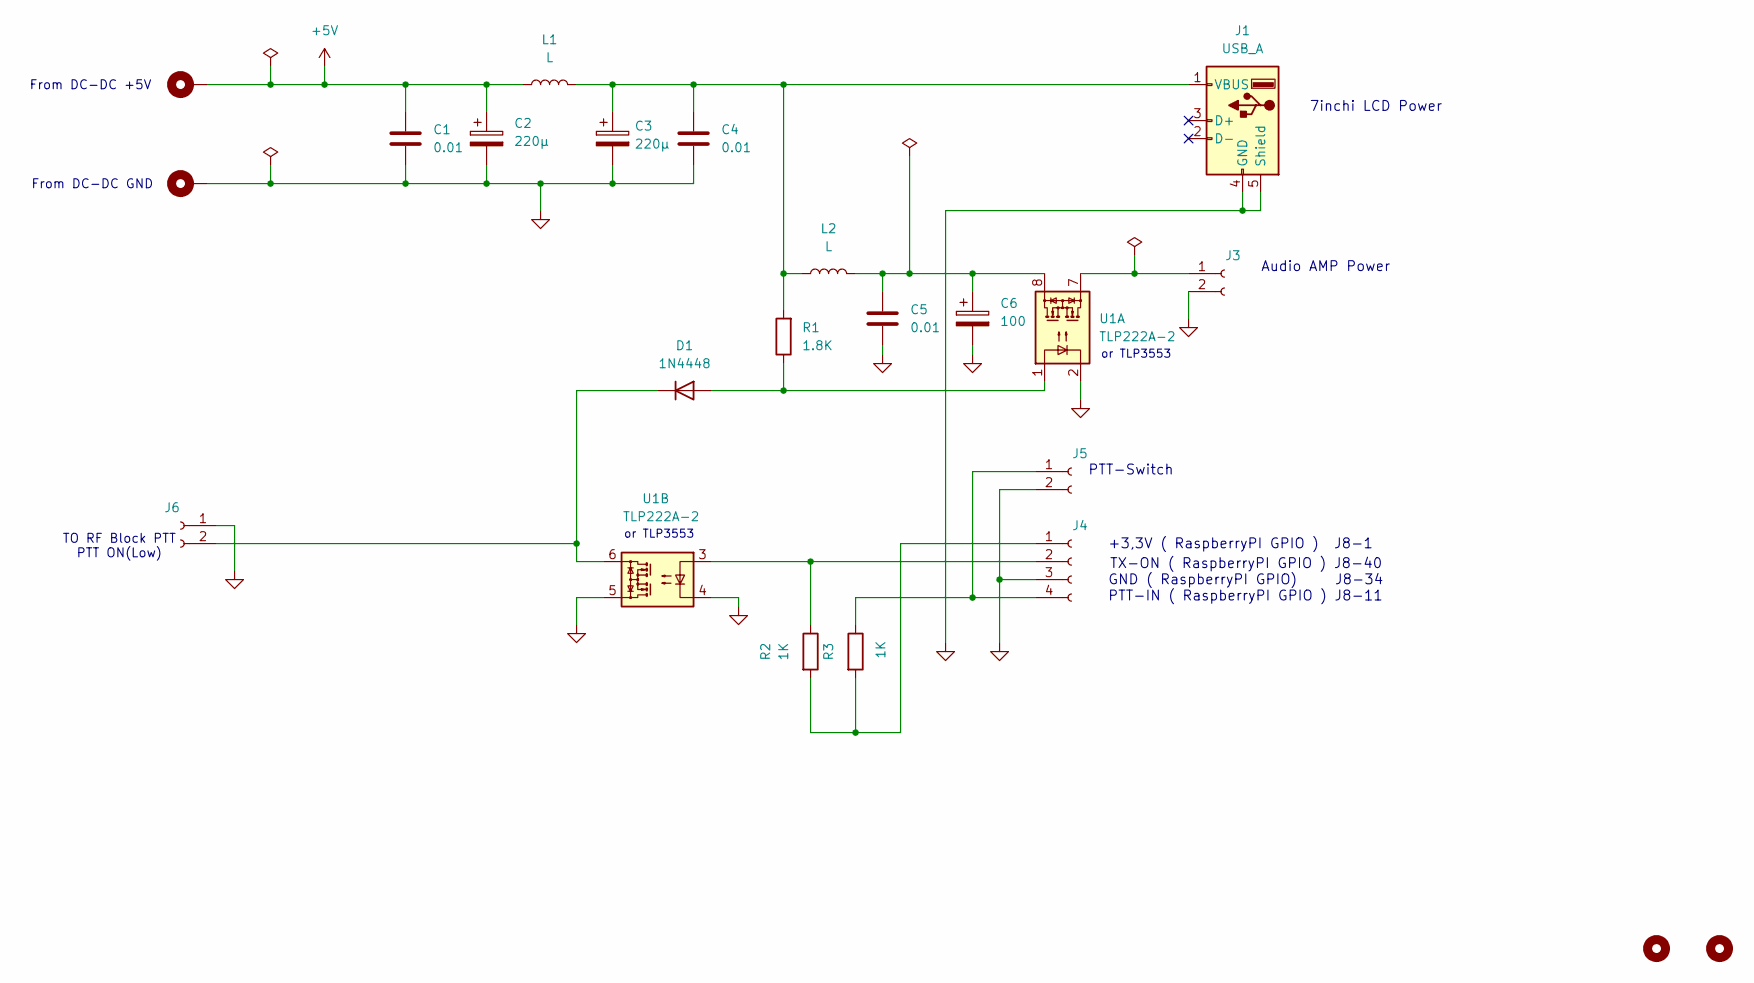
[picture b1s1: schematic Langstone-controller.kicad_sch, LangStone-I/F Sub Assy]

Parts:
C1, C4, C5: 0.01; C_Disc_D4.3mm_W1.9mm_P5.00mm
C2, C3: 220μ; CP_Radial_D6.3mm_P2.50mm
C6: 100; CP_Radial_D6.3mm_P2.50mm
D1: 1N4448; D_DO-35_SOD27_P7.62mm_Horizontal
H1, H2: MountingHole; MountingHole_3.2mm_M3
H3, H4: MountingHole_Pad; MountingHole_2.5mm_Pad
J1: USB_A; USB_A_Molex_67643_Horizontal
J3, J5, J6: Conn_01x02_Female; Molex_KK-254_AE-6410-02A_1x02_P2.54mm_Vertical
J4: Conn_01x04_Female; Molex_KK-254_AE-6410-04A_1x04_P2.54mm_Vertical
L1, L2: L; L_Radial_D10.5mm_P5.00mm_Abacron_AISR-01
R1: 1.8K; R_Axial_DIN0207_L6.3mm_D2.5mm_P5.08mm_Vertical
R2, R3: 1K; R_Axial_DIN0207_L6.3mm_D2.5mm_P5.08mm_Vertical
U1: TLP222A-2; DIP-8_W7.62mm

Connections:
+5V: C1.1, C2.1, H3.1, L1.1
GND: C1.2, C2.2, C3.2, C4.2, C5.2, C6.2, H4.1, J1.4 (GND), J1.5 (Shield), J3.2, J4.3, J5.2, J6.1, U1.2, U1.4, U1.5
unnamed: C5.1, C6.1, L2.2, U1.8
unnamed: D1.2 (A), R1.1, U1.1
unnamed: D1.1 (K), J6.2, U1.6
unnamed: C3.1, C4.1, J1.1 (VBUS), L1.2, L2.1, R1.2
unnamed: J3.1, U1.7
unnamed: J4.1, R2.2, R3.2
unnamed: J4.2, R2.1, U1.3
unnamed: J4.4, J5.1, R3.1

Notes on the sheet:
or TLP3553
GND ( RaspberryPI GPIO) J8-34
TO RF Block PTT PTT ON(Low)
Audio AMP Power
From DC-DC +5V
From DC-DC GND
TX-ON ( RaspberryPI GPIO ) J8-40
PTT-Switch
7inchi LCD Power
+3,3V ( RaspberryPI GPIO ) J8-1
PTT-IN ( RaspberryPI GPIO ) J8-11

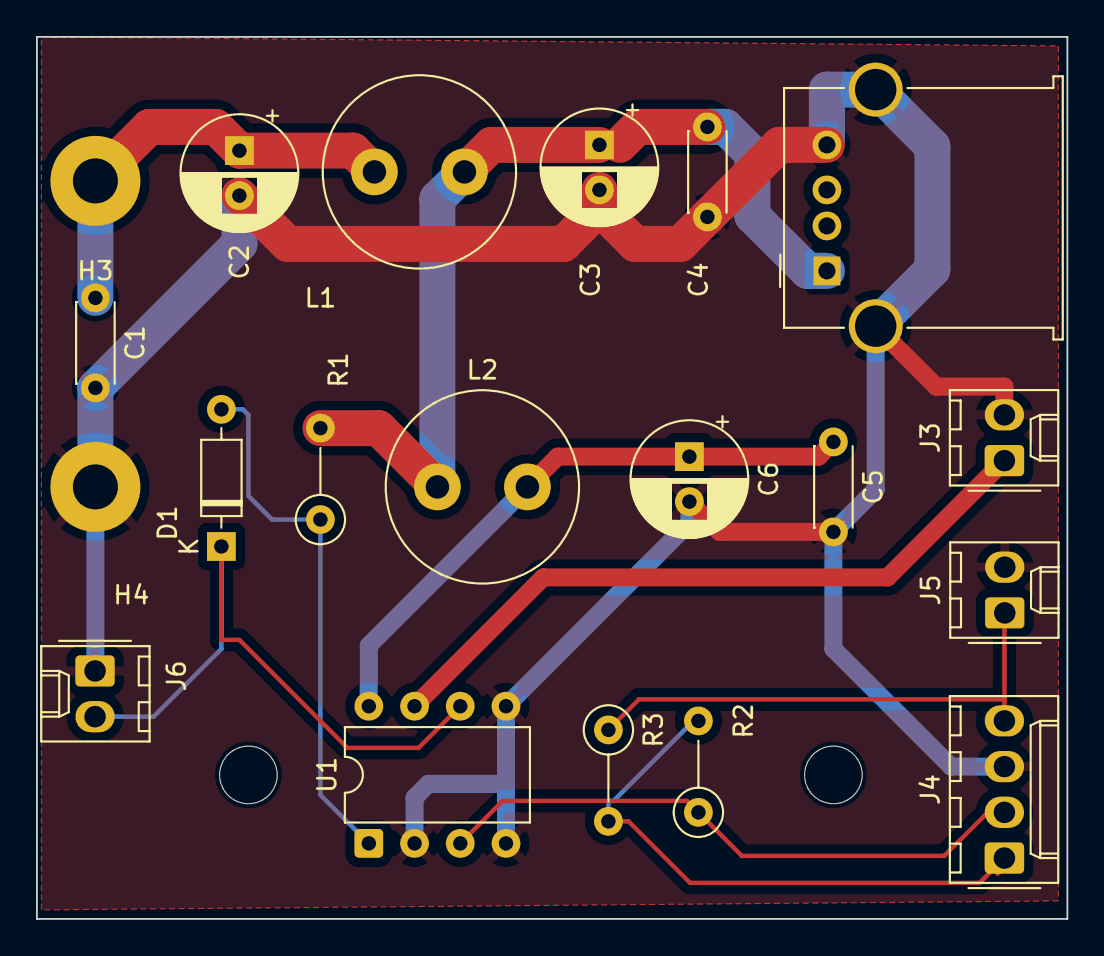
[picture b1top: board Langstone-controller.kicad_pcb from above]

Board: 2 copper layers, 57.2 x 49.0 mm, 22 parts (0 on the bottom side), 10 nets.

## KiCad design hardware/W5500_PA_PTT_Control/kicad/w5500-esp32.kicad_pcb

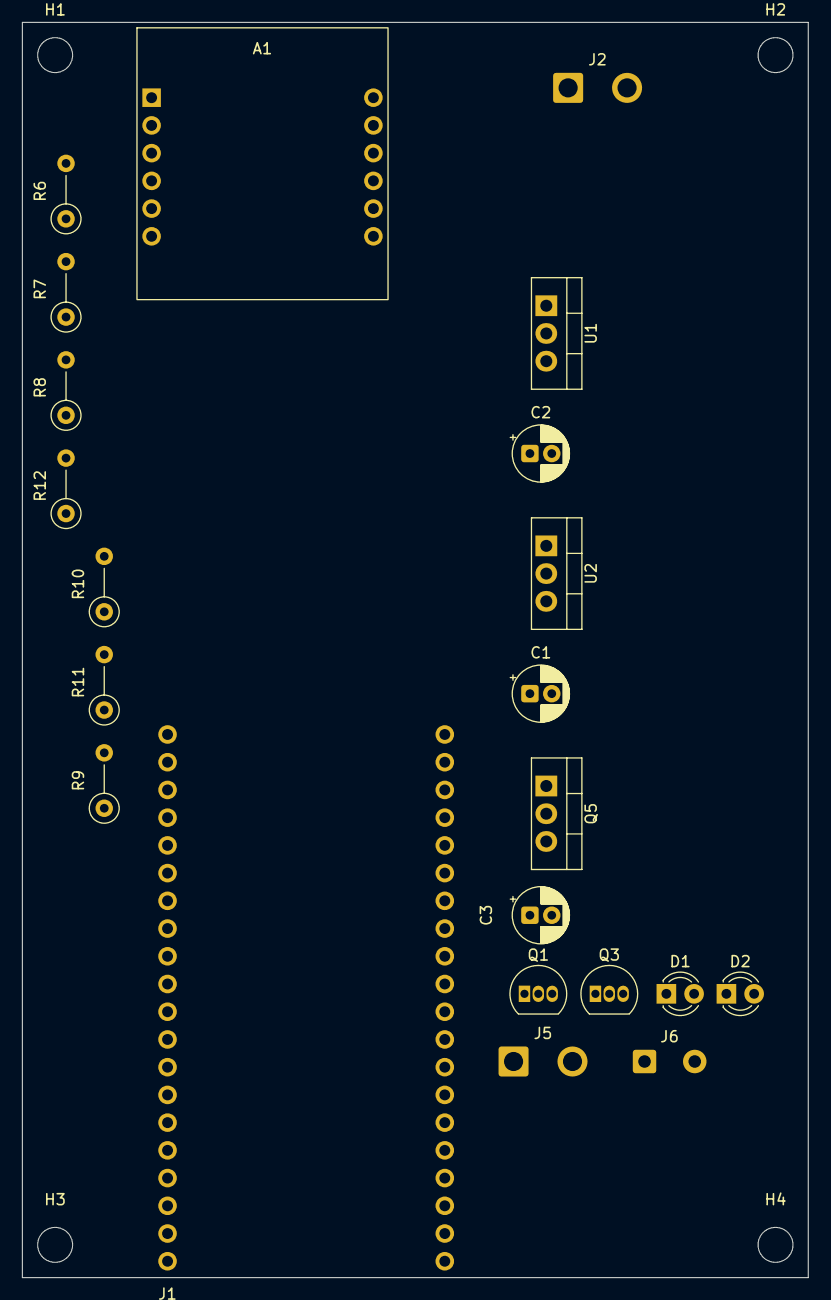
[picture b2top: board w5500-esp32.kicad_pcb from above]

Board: 4 copper layers, 72.0 x 115.0 mm, 26 parts (0 on the bottom side), 19 nets, no tracks yet.

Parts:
A1: W5500_Lite; W5500_Lite_USR-ES1_2x06_P2.54mm_20.32mm
C1, C2, C3: 0.1uF; CP_Radial_D5.0mm_P2.00mm
D1: LED_Red_3mm; LED_D3.0mm
D2: LED_Green_3mm; LED_D3.0mm
H1, H2, H3, H4: MountingHole_3.2mm_M3
J1: ESP32_DevKitC_Socket_40P_25.4mm; Socket_2x20_P2.54mm_25.4mm_DevKitC
J2: DC_IN_13V8; SolderWire-1sqmm_1x02_P5.4mm_D1.4mm_OD2.7mm
J5: Power; SolderWire-1sqmm_1x02_P5.4mm_D1.4mm_OD2.7mm
J6: PTT_ON; SolderWire-0.5sqmm_1x02_P4.6mm_D0.9mm_OD2.1mm
Q1, Q3: 2SC1815; TO-92_Inline
Q5: 2SJ334; TO-220-3_Vertical
R6, R7: 510; R_Axial_DIN0207_L6.3mm_D2.5mm_P5.08mm_Vertical
R8: 1k; R_Axial_DIN0207_L6.3mm_D2.5mm_P5.08mm_Vertical
R9, R10, R11, R12: 10k; R_Axial_DIN0207_L6.3mm_D2.5mm_P5.08mm_Vertical
U1: TA48033S; TO-220-3_Vertical
U2: L7805; TO-220-3_Vertical

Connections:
+12V: C3.1, J2.1, Q5.3 (S), R8.2, R11.1, U2.1 (IN)
/+3V3_A: A1.8, A1.9, C2.1, R9.1, U1.2 (OUT)
/+5v0: C1.1, J1.1 (5V), J1.2 (5V), U1.1 (IN), U2.3 (OUT)
/GPIO21_W5500_RST: A1.11, J1.35 (GPIO21), R9.2
/GPIO26_PA: J1.11 (GPIO26), R6.1
/GPIO27_PTT: J1.10 (GPIO27), R7.1
/PTT_ON: J6.1, Q3.2 (C)
/Power: J5.1, Q5.2 (D), R10.1
<NO NET>: D1.1 (K), J1.7 (GND)
GND: A1.1, A1.2, A1.7, C1.2, C2.2, C3.2, D2.1 (K), J2.2, J5.2, J6.2, Q1.1 (E), Q3.1 (E), R12.2, U1.3 (GND), U2.2 (GND)
unnamed: A1.5, J1.31 (GPIO5)
unnamed: A1.12, J1.33 (GPIO19)
unnamed: A1.3, J1.39 (GPIO23)
unnamed: A1.4, J1.32 (GPIO18)
unnamed: D1.2 (A), R10.2
unnamed: D2.2 (A), R11.2
unnamed: Q1.3 (B), R6.2, R12.1
unnamed: Q1.2 (C), Q5.1 (G), R8.1
unnamed: Q3.3 (B), R7.2

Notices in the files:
README.md:
License:
本ソフトウェアはGNU General Public License v3.0(GPLv3)の下で提供されます。
ライセンス全文: [LICENSE](LICENSE)
This software is licensed under the GNU General Public License v3.0 (GPLv3).
Full license text: [LICENSE](LICENSE)
- Langstone V3 (SDR transceiver, [g4eml/Langstone-V3](https://github.com/g4eml/Langstone-V3)): GPLv3
- Reception subsystem design (Shinji Yamazaki, JE1BTA): GPLv3
- Application development, reception stability fixes (Kazuichi Shinjo): GPLv3
